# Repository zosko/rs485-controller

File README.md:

# ModBus
Controlling device with RS485 protocol

## Sponsorship

This project is kindly sponsored by [PCBWay](https://pcbway.com).
PCBWay specializes in manufacturing high-quality PCBs and makes them affordable to hobbyist and professionals alike.

The range of services they offer include PCB prototyping, assembly, instant quotes for your order, a verification process by a team
of experts and an easy to use, hassle-free order process.

I'm grateful to PCBWay for the support in creating this project.

## PCB

## KiCad

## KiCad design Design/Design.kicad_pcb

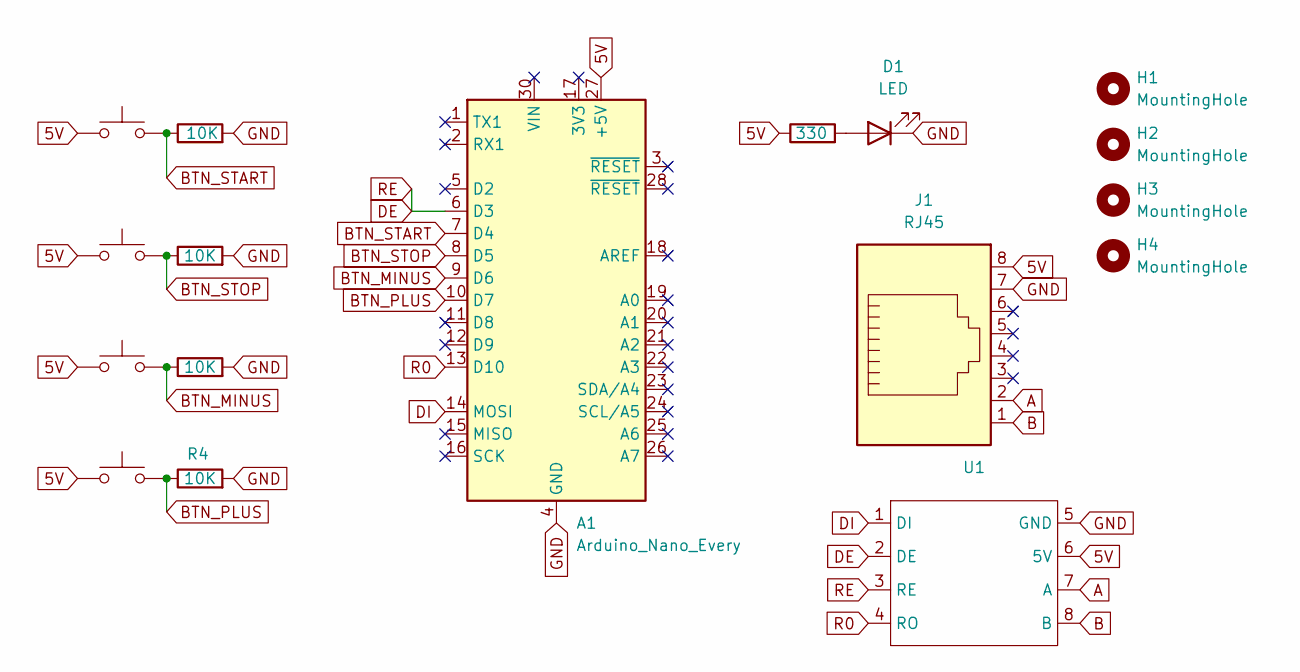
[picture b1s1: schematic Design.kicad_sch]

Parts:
A1: Arduino_Nano_Every; Arduino_Nano
D1: LED; LED_D5.0mm
H1, H2, H3, H4: MountingHole; MountingHole_5mm
J1: RJ45; RJ45_Amphenol_54602-x08_Horizontal
R1, R2, R3, R4: 10K; R_Axial_DIN0207_L6.3mm_D2.5mm_P7.62mm_Horizontal
R5: 330; R_Axial_DIN0207_L6.3mm_D2.5mm_P7.62mm_Horizontal
SW1, SW2, SW3, SW4: SW_Push; SW_PUSH-12mm
U1: MAX485-TTL

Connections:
5V: A1.27 (+5V), J1.8, R5.1, SW1.1, SW2.1, SW3.1, SW4.1, U1.6 (5V)
A: J1.2, U1.7 (A)
B: J1.1, U1.8 (B)
BTN_MINUS: A1.9 (D6), R3.1, SW3.2
BTN_PLUS: A1.10 (D7), R4.1, SW4.2
BTN_START: A1.7 (D4), R1.1, SW1.2
BTN_STOP: A1.8 (D5), R2.1, SW2.2
DE: A1.6 (D3), U1.2 (DE), U1.3 (RE)
DI: A1.14 (MOSI), U1.1 (DI)
GND: A1.4 (GND), A1.29 (GND), D1.1 (K), J1.7, R1.2, R2.2, R3.2, R4.2, U1.5 (GND)
unnamed: D1.2 (A), R5.2
R0: A1.13 (D10), U1.4 (RO)

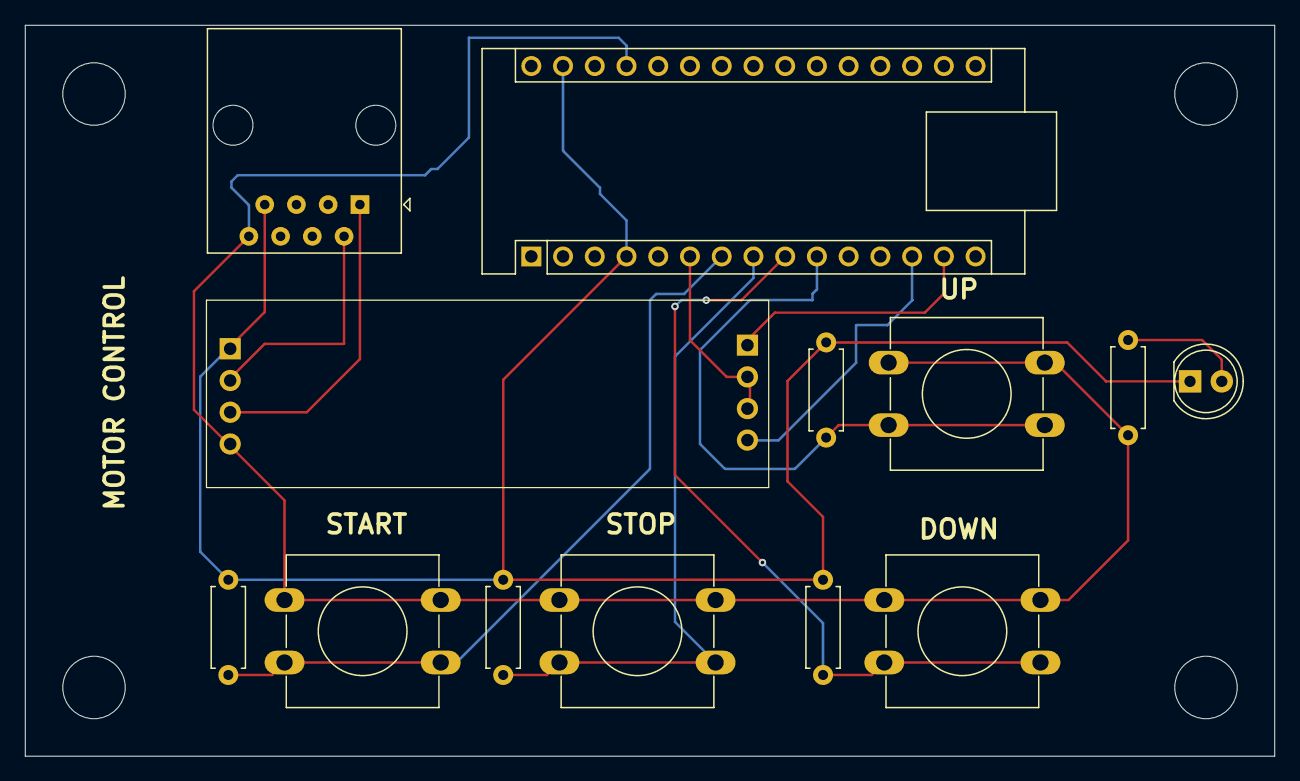
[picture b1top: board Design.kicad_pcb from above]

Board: 2 copper layers, 100.0 x 58.5 mm, 17 parts (0 on the bottom side), 12 nets.
